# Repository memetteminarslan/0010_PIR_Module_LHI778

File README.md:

# 0010_PIR_Module_LHI778

You are seeing a large number of widely used PIR modules in electronic development kits. More information coming soon...

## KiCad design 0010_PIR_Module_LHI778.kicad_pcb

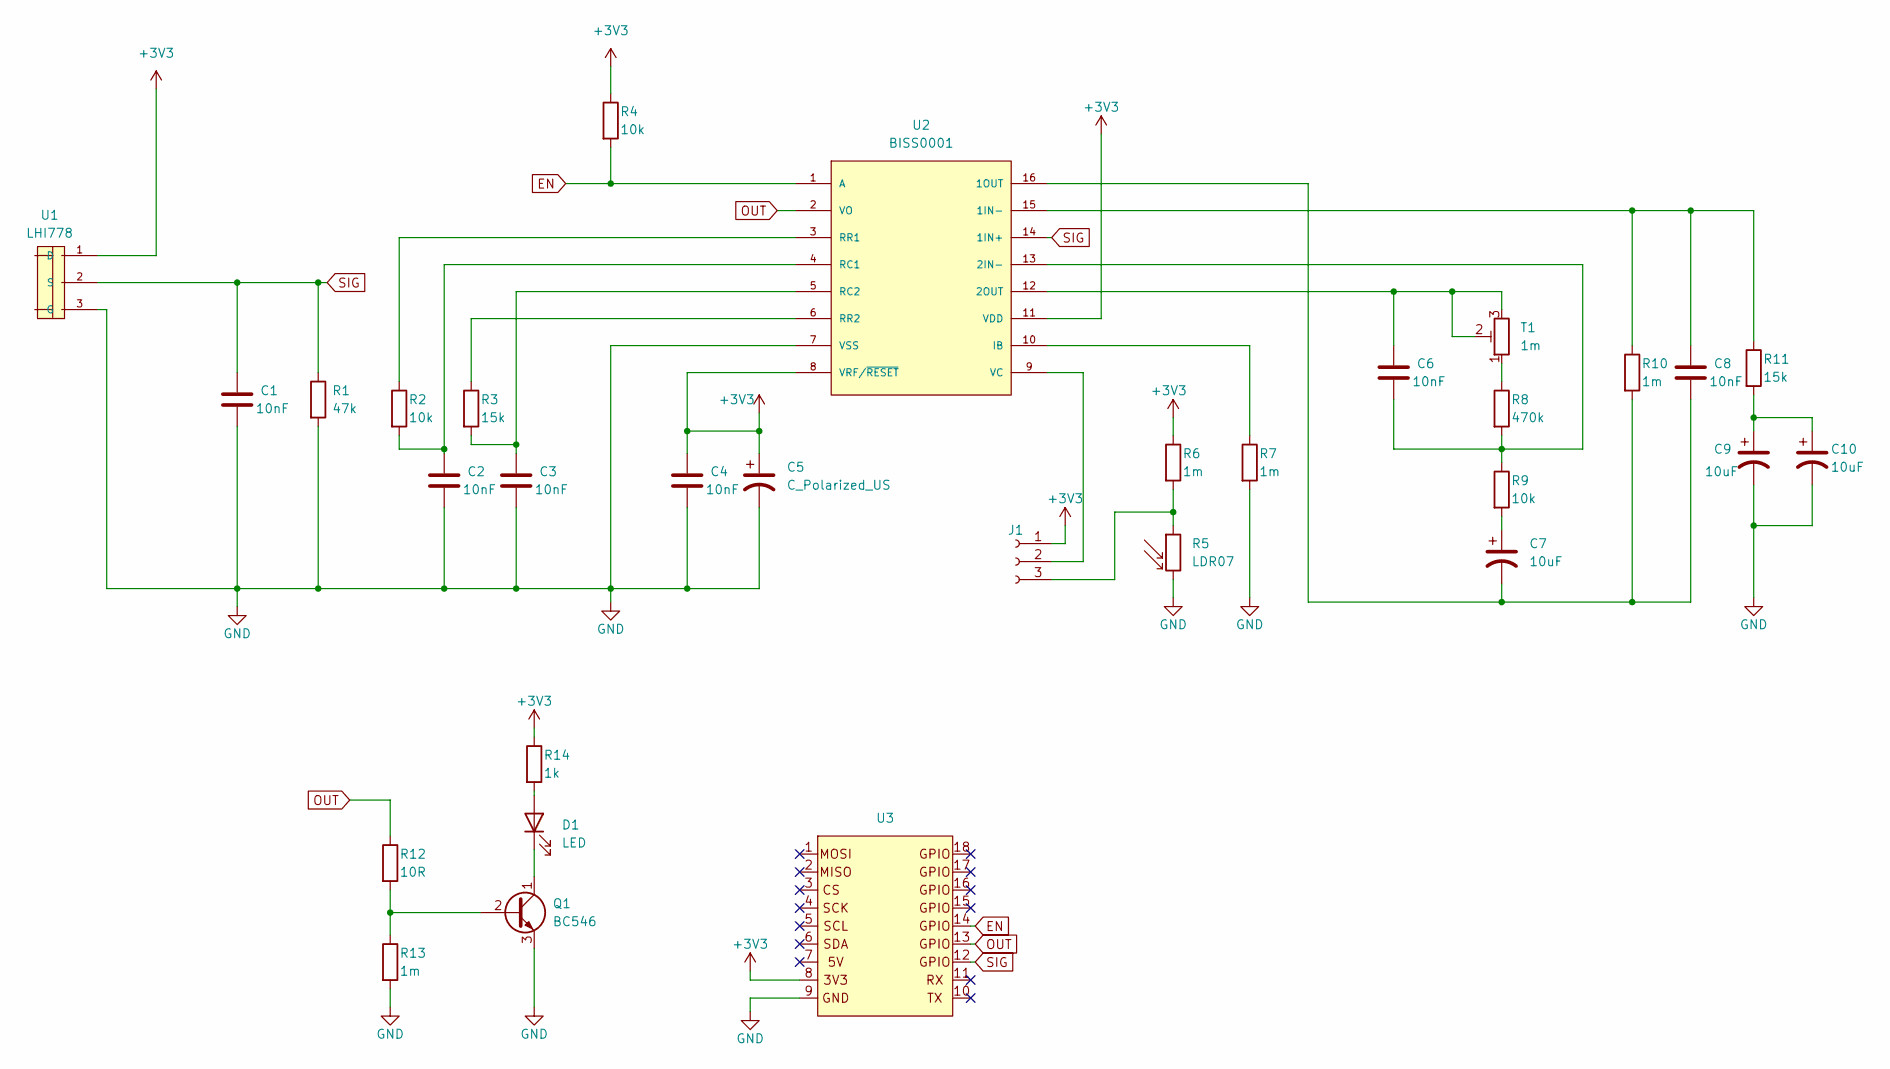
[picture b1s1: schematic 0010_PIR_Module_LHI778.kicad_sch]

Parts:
C1, C2, C3, C4, C6: 10nF; C_0603_1608Metric
C5: C_Polarized_US; CP_EIA-1608-08_AVX-J
C7, C9, C10: 10uF; CP_EIA-1608-08_AVX-J
C8: 10nF; C_0603_1608Metric_Pad1.08x0.95mm_HandSolder
D1: LED; LED_0603_1608Metric
J1: Conn_01x03_Female; SolderJumper-3_P1.3mm_Open_Pad1.0x1.5mm_NumberLabels
Q1: BC546; SOT-23
R1: 47k; R_0603_1608Metric
R2, R4, R9: 10k; R_0603_1608Metric
R3, R11: 15k; R_0603_1608Metric
R5: LDR07; R_LDR_5.1x4.3mm_P3.4mm_Vertical
R6, R7, R10, R13: 1m; R_0603_1608Metric
R8: 470k; R_0603_1608Metric
R12: 10R; R_0603_1608Metric
R14: 1k; R_0603_1608Metric
T1: 1m; 3362P_1
U1: LHI778; SNR3-D8.1XH4.2MM; MPN LHI778
U2: BISS0001; SOIC127P600X180-16N
U3: pin_header

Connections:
+3V3: C4.1, C5.1, J1.1, R4.1, R6.1, R14.1, U1.1 (D), U2.8 (VRF/~RESET), U2.11 (VDD), U3.8
EN: R4.2, U2.1 (A), U3.14
GND: C1.2, C2.2, C3.2, C4.2, C5.2, C9.2, C10.2, Q1.3 (E), R1.2, R5.2, R7.2, R13.2, U1.3 (G), U2.7 (VSS), U3.9
unnamed: C7.1, R9.2
unnamed: C9.1, C10.1, R11.2
unnamed: D1.2 (A), R14.2
unnamed: D1.1 (K), Q1.1 (C)
unnamed: J1.2, U2.9 (VC)
unnamed: J1.3, R5.1, R6.2
unnamed: Q1.2 (B), R12.2, R13.1
unnamed: R8.1, T1.1
unnamed: C8.1, R10.1, R11.1, U2.15 (1IN-)
unnamed: C7.2, C8.2, R10.2, U2.16 (1OUT)
unnamed: C6.2, R8.2, R9.1, U2.13 (2IN-)
unnamed: C6.1, T1.2, T1.3, U2.12 (2OUT)
unnamed: R7.1, U2.10 (IB)
unnamed: C2.1, R2.2, U2.4 (RC1)
unnamed: C3.1, R3.2, U2.5 (RC2)
unnamed: R2.1, U2.3 (RR1)
unnamed: R3.1, U2.6 (RR2)
OUT: R12.1, U2.2 (VO), U3.13
SIG: C1.1, R1.1, U1.2 (S), U2.14 (1IN+), U3.12

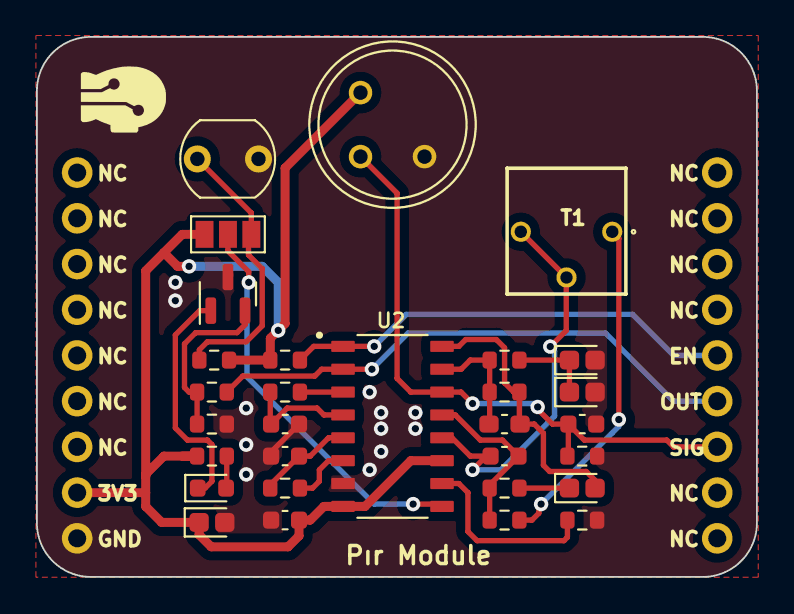
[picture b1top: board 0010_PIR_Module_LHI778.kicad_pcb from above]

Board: 2 copper layers, 40.0 x 30.0 mm, 31 parts (0 on the bottom side), 22 nets.
